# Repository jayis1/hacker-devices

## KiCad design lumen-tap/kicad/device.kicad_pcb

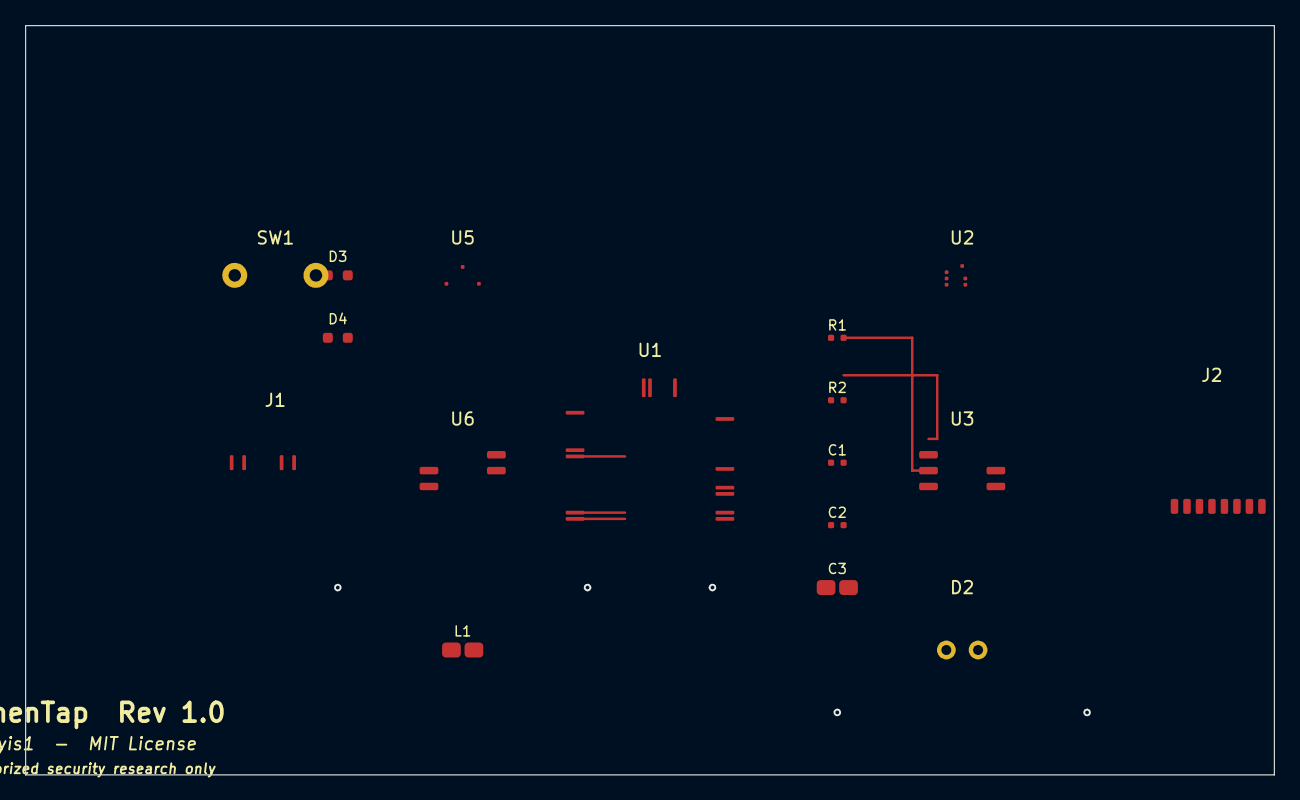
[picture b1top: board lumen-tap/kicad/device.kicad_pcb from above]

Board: 4 copper layers, 100.0 x 60.0 mm, 17 parts (0 on the bottom side), 14 nets.

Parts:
C1, C2: 100nF; C_0402_1005Metric
C3: 10uF; C_0805_2012Metric
D2: S1223; TO-5-2_Window
D3: LED_GREEN; LED_0603_1608Metric
D4: LED_RED; LED_0603_1608Metric
J1: USB_C; USB_C_Receptacle_HRO_TYPE-C-31-M-12
J2: Micro_SD_Card; microSD_HC_Hirose_DM3D-SF
L1: 4u7H; L_0805_2012Metric
R1: 10k; R_0402_1005Metric
R2: 100; R_0402_1005Metric
SW1: SW_SPST_KEYED; SW_PUSH_6mm
U1: STM32H743VIT6; LQFP-100_14x14mm_P0.5mm
U2: iC-HK; QFN-16-1EP_3x3mm_P0.5mm
U3: OPA380; SOIC-8_3.9x4.9mm_P1.27mm
U5: LT3045IDE; DFN-12-1EP_3x3mm_P0.45mm
U6: MP1584EN; SOIC-8_3.9x4.9mm_P1.27mm

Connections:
ARM_KEY: SW1.1, U1.39
GND: C1.2, C2.2, C3.2, D3.2, D4.2, J1.A1, J2.6, R2.2, U1.10, U2.16, U3.4, U5.11, U6.1
LASER_A: R2.1, U2.5
LASER_EN: U1.40, U2.3
LASER_PWM: U1.26, U2.2
LED_FAULT: D4.1, U1.36
LED_STATUS: D3.1, U1.35
PD_ANODE: D2.2, R1.1, U3.3
SD_CLK: J2.5, U1.51
TIA_OUT: R1.2, U3.2, U3.6
VBUS: J1.A4, U1.27
VCC_3V3: C1.1, J2.4, L1.2, SW1.2, U1.11, U6.6, U6.7
VCC_5V: C3.1, L1.1, U5.1, U6.2
VCC_5V_CLEAN: C2.1, U2.1, U3.7, U5.2

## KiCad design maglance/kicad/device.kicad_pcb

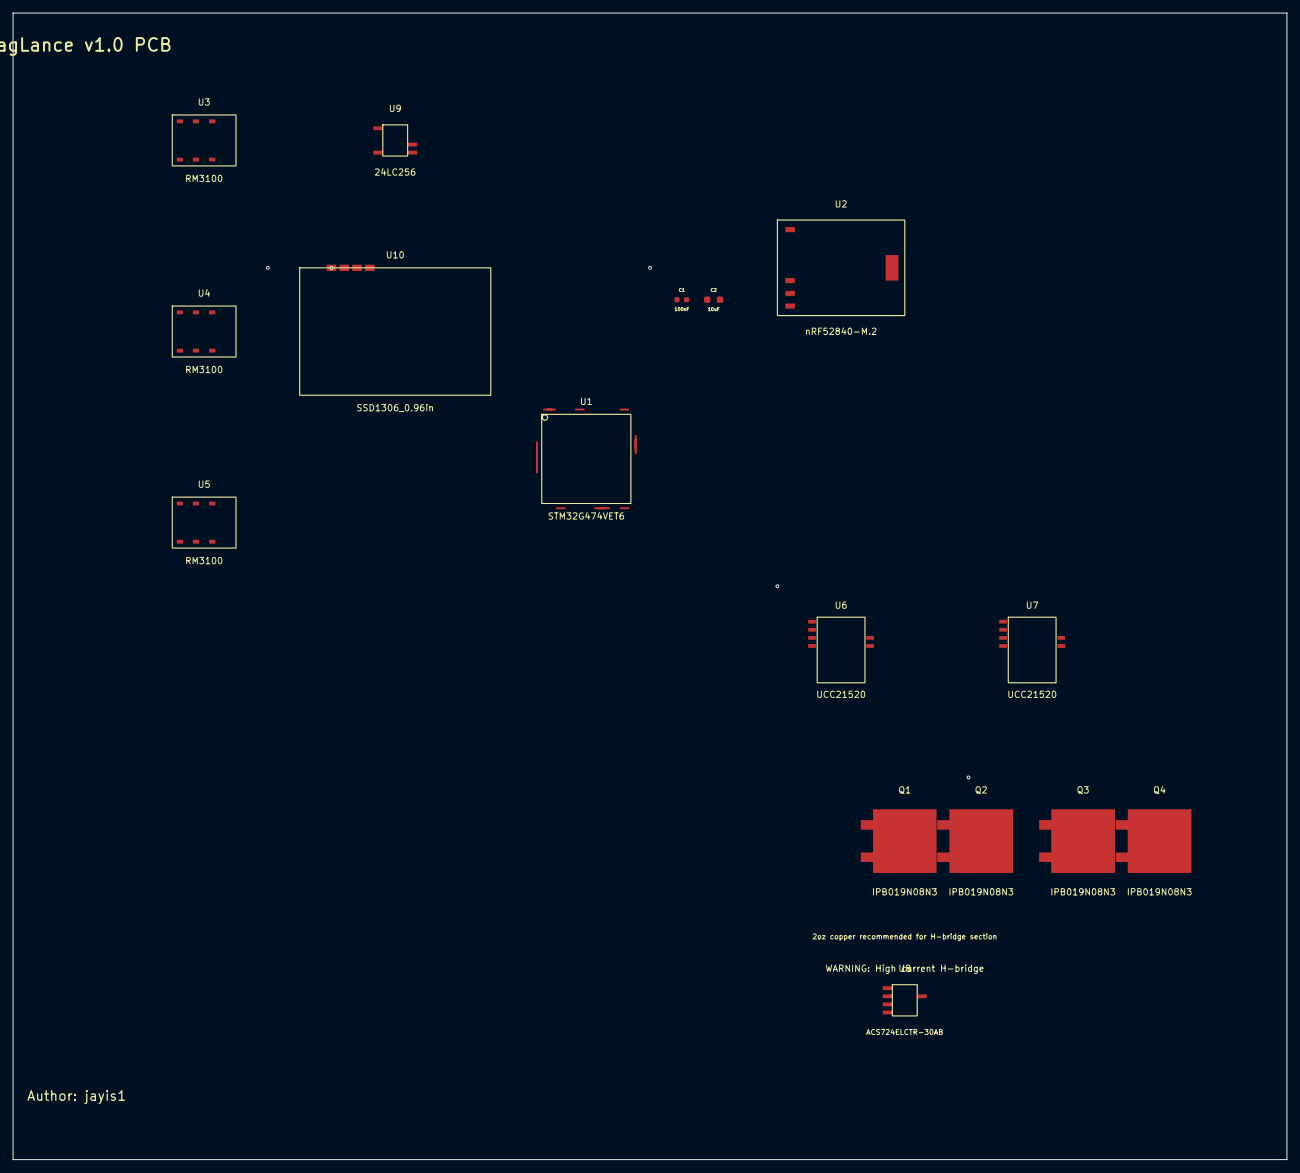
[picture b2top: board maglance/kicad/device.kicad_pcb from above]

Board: 4 copper layers, 200.0 x 180.0 mm, 16 parts (0 on the bottom side), 21 nets, no tracks yet.

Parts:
C1: 100nF; C_0603_1608Metric
C2: 10uF; C_0805_2012Metric
Q1, Q2, Q3, Q4: IPB019N08N3; TO-263-3_TabPin2
U1: STM32G474VET6; LQFP-100_14x14mm_P0.5mm
U2: nRF52840-M.2; Nordic_nRF52840_M2
U3, U4, U5: RM3100; PNI_RM3100
U6, U7: UCC21520; SOIC-16W_7.5x10.3mm_P1.27mm
U8: ACS724ELCTR-30AB; SOIC-8_3.9x4.9mm_P1.27mm
U9: 24LC256; SOIC-8_3.9x4.9mm_P1.27mm
U10: SSD1306_0.96in; OLED_0.96in_128x64

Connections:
+5V: C1.1, C2.1, Q1.2, Q4.2, U1.11, U2.1, U3.1, U4.1, U5.1, U6.1, U7.1, U8.1, U9.8, U10.1
ADC_CURRENT: U1.14, U8.3
COIL+: Q1.3, Q2.2, U8.4
COIL-: Q3.2, Q4.3, U8.5
GATE_Q1: Q1.1, U6.5
GATE_Q2: Q2.1, U6.6
GATE_Q3: Q3.1, U7.5
GATE_Q4: Q4.1, U7.6
GND: C1.2, C2.2, Q2.3, Q3.3, U1.2, U1.27, U2.2, U3.2, U4.2, U5.2, U6.2, U7.2, U8.2, U9.4, U10.2
HRTIM_CHA1: U1.41, U6.3
HRTIM_CHA2: U1.42, U6.4
HRTIM_CHC1: U1.43, U7.3
HRTIM_CHC2: U1.44, U7.4
I2C1_SCL: U1.59, U9.6, U10.3
I2C1_SDA: U1.60, U9.5, U10.4
MAG_CS0: U1.56, U3.6
MAG_CS1: U1.57, U4.6
MAG_CS2: U1.58, U5.6
SPI2_MISO: U1.54, U3.4, U4.4, U5.4
SPI2_MOSI: U1.55, U3.5, U4.5, U5.5
SPI2_SCK: U1.53, U3.3, U4.3, U5.3

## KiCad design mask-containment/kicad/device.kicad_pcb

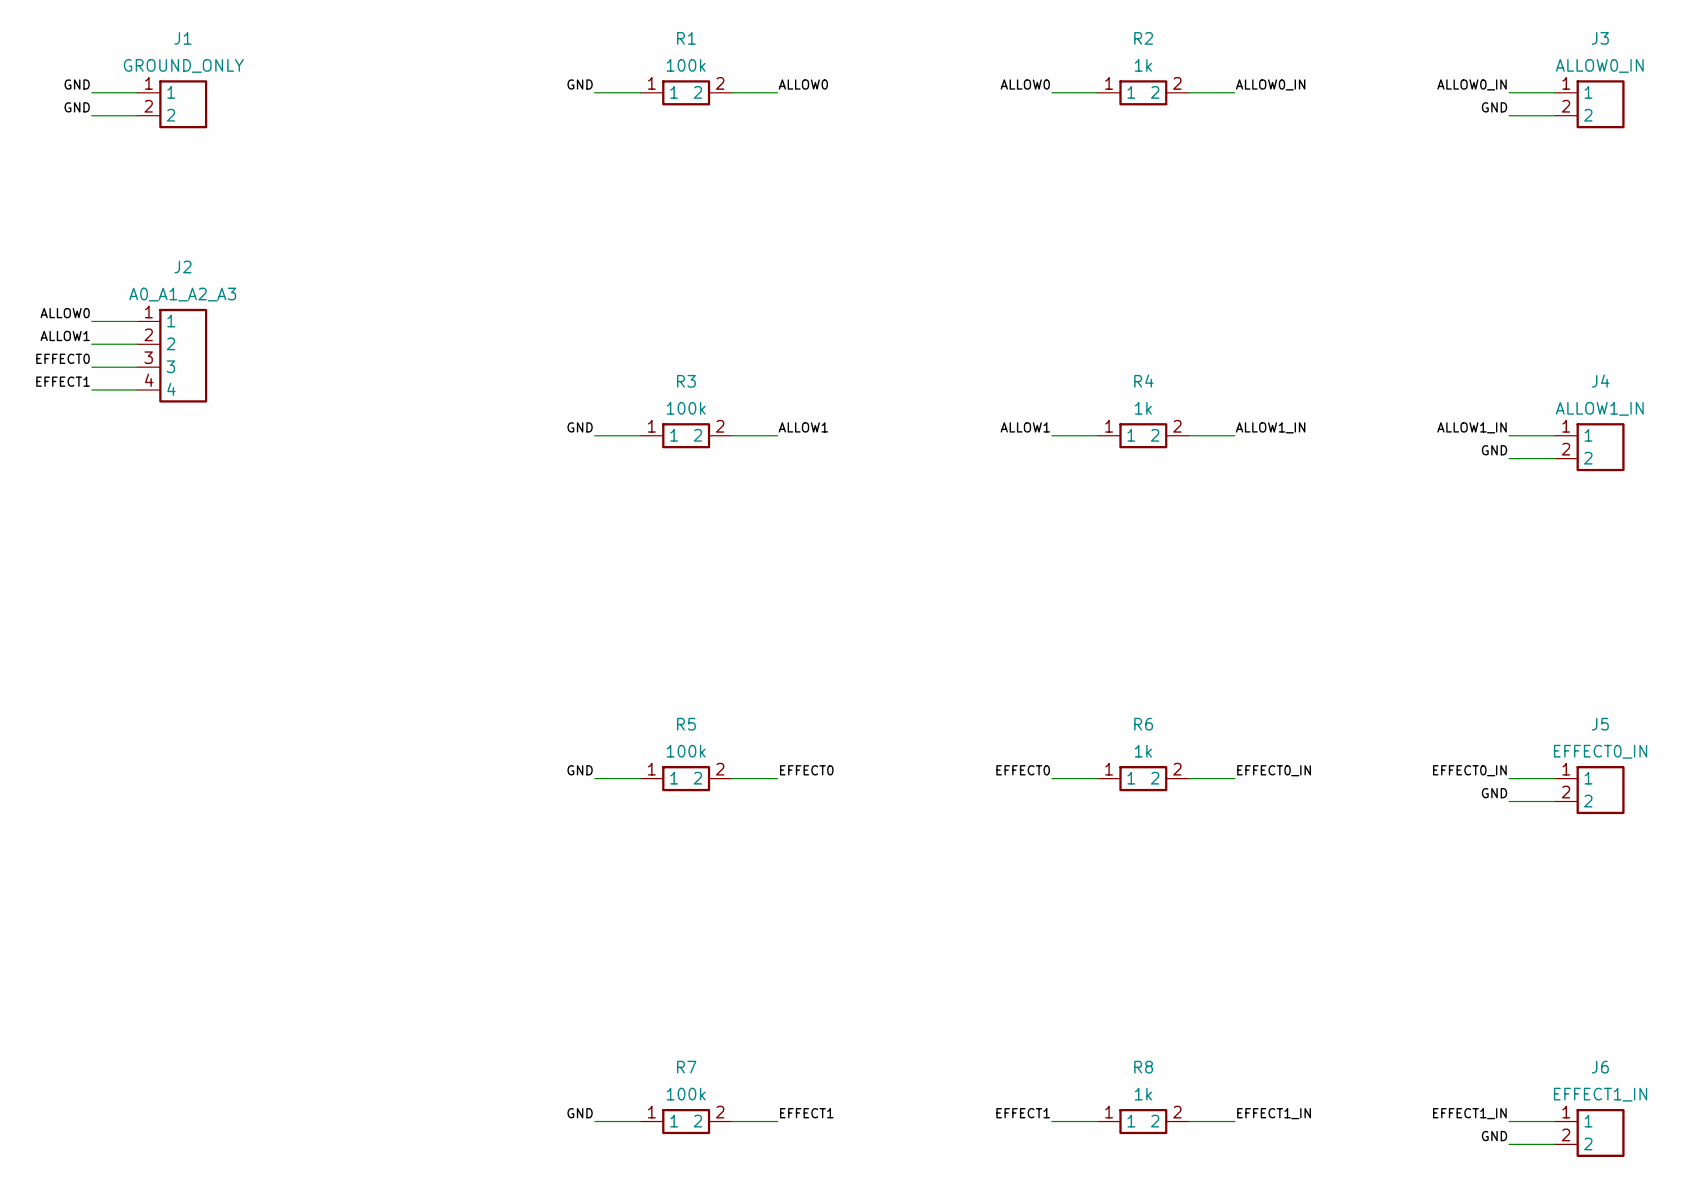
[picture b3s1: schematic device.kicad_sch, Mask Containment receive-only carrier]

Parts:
J1: GROUND_ONLY; PinHeader_1x02_P2.54mm_Vertical
J2: A0_A1_A2_A3; PinHeader_1x04_P2.54mm_Vertical
J3: ALLOW0_IN; PinHeader_1x02_P2.54mm_Vertical
J4: ALLOW1_IN; PinHeader_1x02_P2.54mm_Vertical
J5: EFFECT0_IN; PinHeader_1x02_P2.54mm_Vertical
J6: EFFECT1_IN; PinHeader_1x02_P2.54mm_Vertical
R1, R3, R5, R7: 100k; R_Axial_DIN0207_L6.3mm_D2.5mm_P7.62mm_Horizontal
R2, R4, R6, R8: 1k; R_Axial_DIN0207_L6.3mm_D2.5mm_P7.62mm_Horizontal

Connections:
ALLOW0: J2.1, R1.2, R2.1
ALLOW0_IN: J3.1, R2.2
ALLOW1: J2.2, R3.2, R4.1
ALLOW1_IN: J4.1, R4.2
EFFECT0: J2.3, R5.2, R6.1
EFFECT0_IN: J5.1, R6.2
EFFECT1: J2.4, R7.2, R8.1
EFFECT1_IN: J6.1, R8.2
GND: J1.1, J1.2, J3.2, J4.2, J5.2, J6.2, R1.1, R3.1, R5.1, R7.1

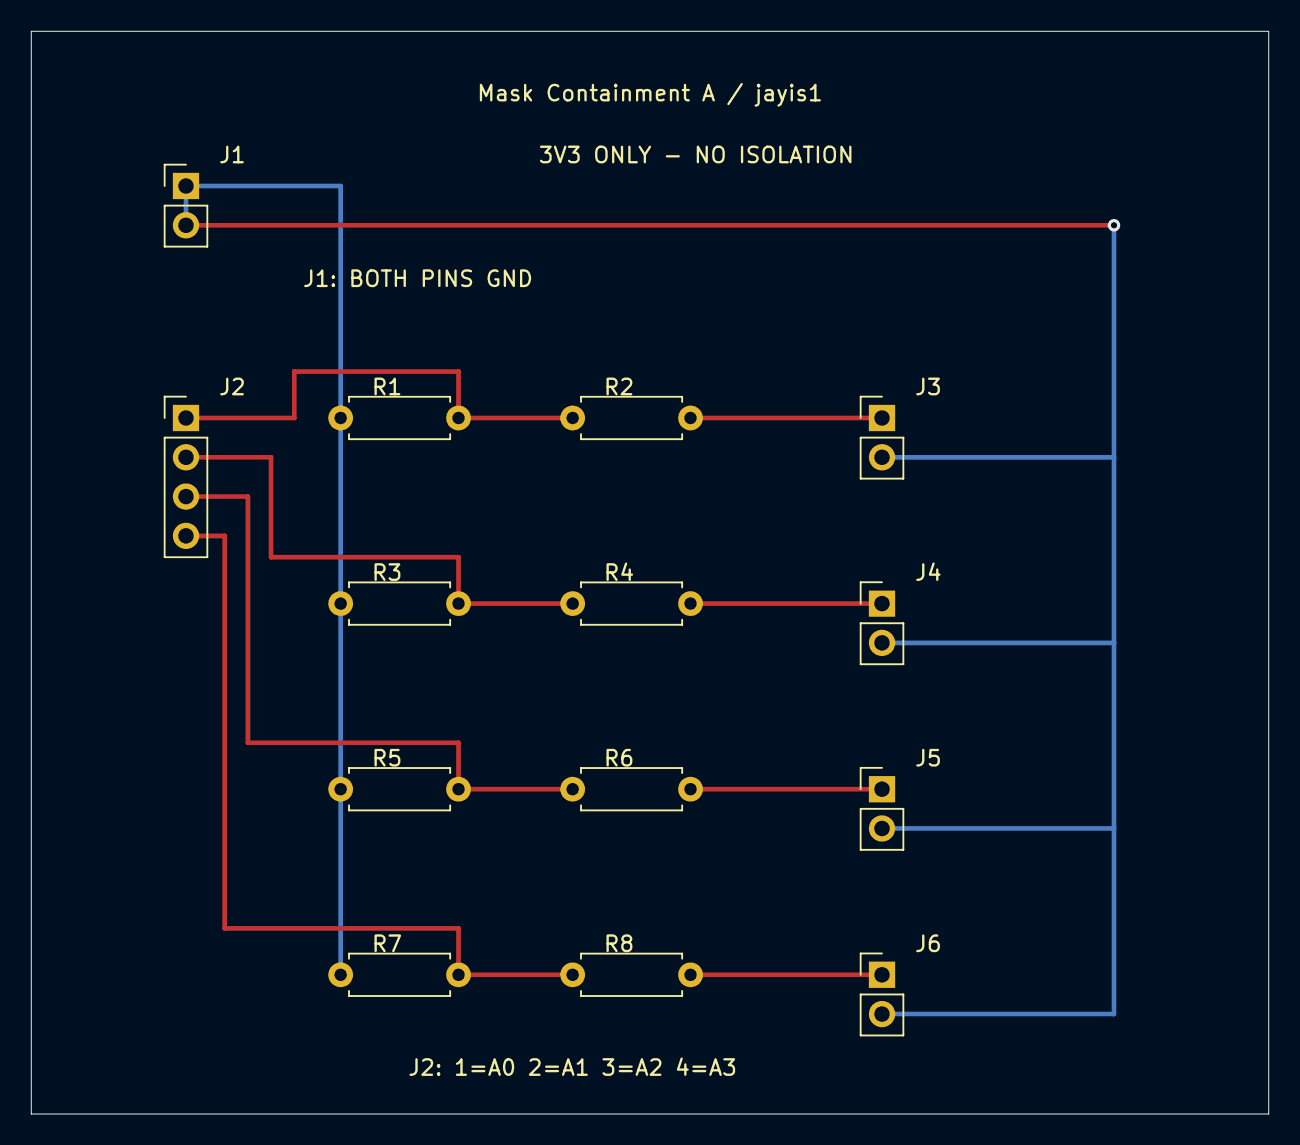
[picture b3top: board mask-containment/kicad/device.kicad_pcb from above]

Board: 2 copper layers, 80.0 x 70.0 mm, 14 parts (0 on the bottom side), 9 nets.

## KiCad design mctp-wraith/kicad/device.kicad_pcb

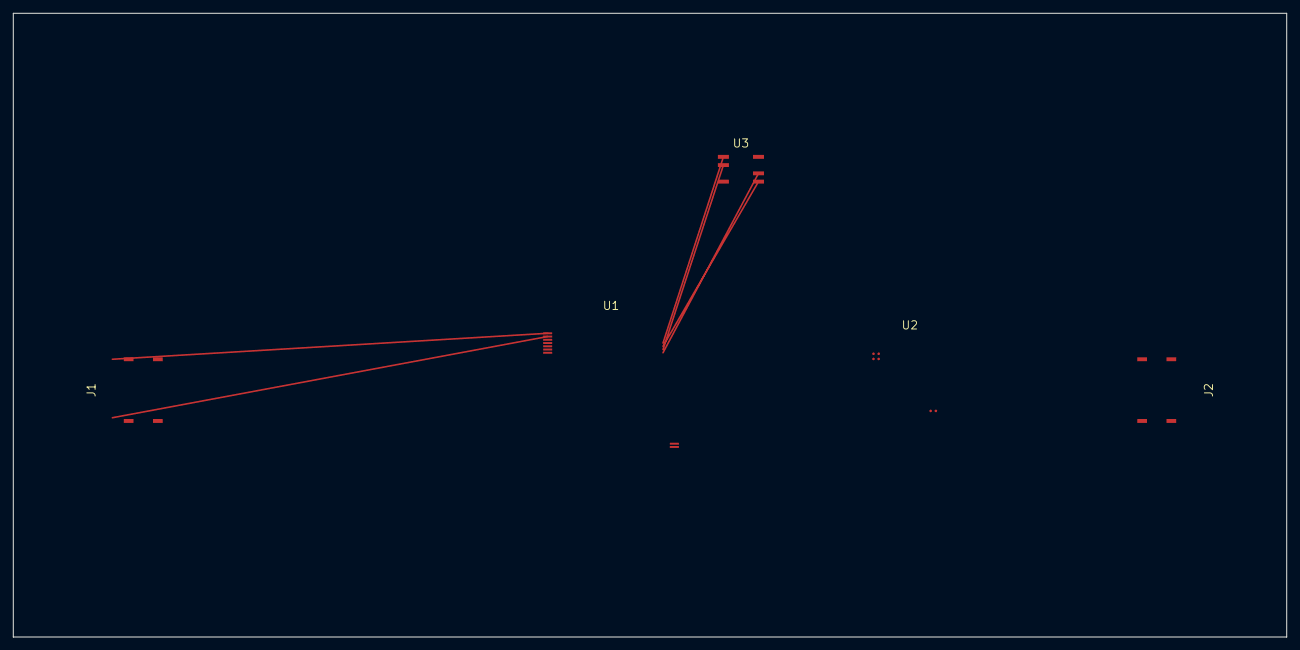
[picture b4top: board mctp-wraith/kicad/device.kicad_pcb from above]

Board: 2 copper layers, 196.0 x 96.0 mm, 5 parts (0 on the bottom side), 11 nets.

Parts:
J1: UPSTREAM_SIDEBAND; Samtec_QSH-020-01-L-D-A
J2: DOWNSTREAM_SIDEBAND; Samtec_QSH-020-01-L-D-A
U1: STM32H753ZITx; LQFP-144_20x20mm_P0.5mm
U2: LFE5U-25F; caBGA-256_14x14_0.8mm
U3: W25Q128JVSIQ; SOIC-8_5.23x5.23mm_P1.27mm

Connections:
ALERT_N: J1.19, J2.19, U1.7
GND: J1.20, J2.20, U1.73, U2.N12, U3.4
I3C_SCL_DN: J2.1, U2.A1
I3C_SCL_UP: J1.1, U1.1, U2.B1
I3C_SDA_DN: J2.2, U2.A2
I3C_SDA_UP: J1.2, U1.2, U2.B2
QSPI_CLK: U1.4, U3.6
QSPI_CS: U1.3, U3.1
QSPI_IO0: U1.5, U3.2
QSPI_IO1: U1.6, U3.5
VCC_3V3: U1.72, U2.M12, U3.8

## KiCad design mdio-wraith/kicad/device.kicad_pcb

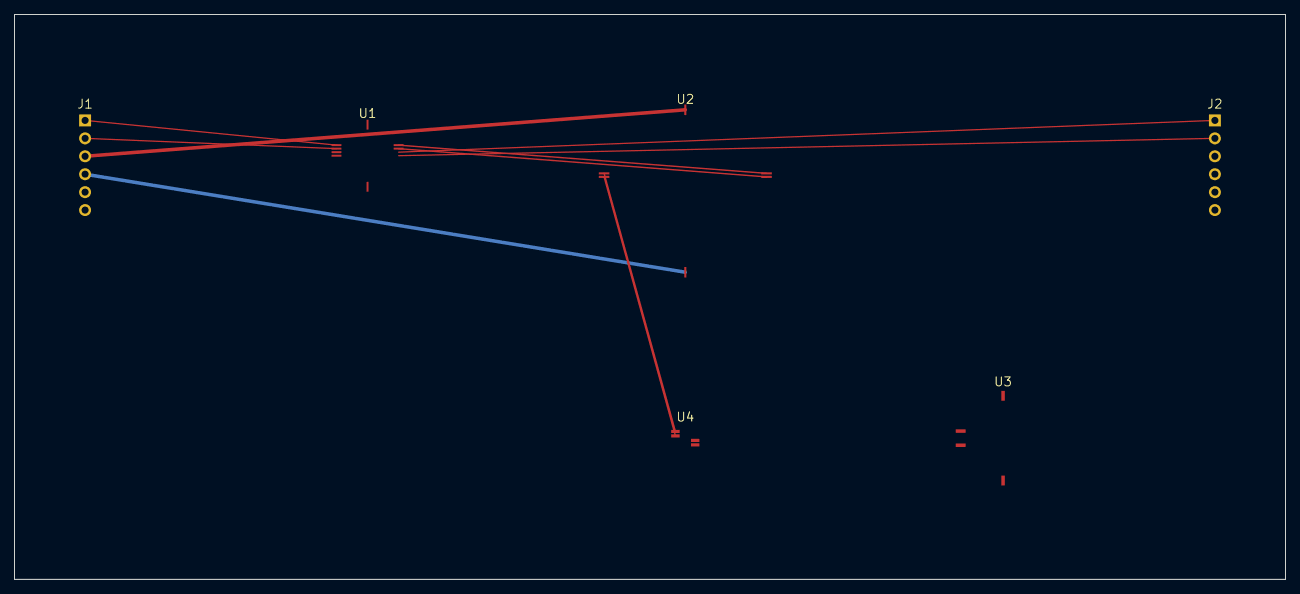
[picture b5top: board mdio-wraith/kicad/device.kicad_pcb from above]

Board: 2 copper layers, 180.0 x 80.0 mm, 6 parts (0 on the bottom side), 10 nets.

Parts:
J1: HOST_MDIO_CLIP; PinHeader_1x06_P2.54mm_Vertical
J2: PHY_MDIO_CLIP; PinHeader_1x06_P2.54mm_Vertical
U1: CrossLink-NX; LQFP-48_7x7mm_P0.5mm
U2: STM32H723ZGT6; LQFP-144_20x20mm_P0.5mm
U3: ESP32-C6-MINI-1
U4: INA232AIDDFR; SOT-23-8

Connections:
3V3: J1.3, J2.3, U1.62, U2.13, U3.1, U4.6
GND: J1.4, J2.4, U1.31, U2.64, U3.15, U4.5
I2C_SCL: J2.5, U2.95, U4.1
I2C_SDA: J2.6, U2.96, U4.2
MDC_HOST: J1.2, U1.6
MDC_PHY: J2.2, U1.8
MDIO_HOST: J1.1, U1.5
MDIO_PHY: J2.1, U1.7
UART_RX: J1.6, U1.45, U2.52, U3.31
UART_TX: J1.5, U1.44, U2.51, U3.30

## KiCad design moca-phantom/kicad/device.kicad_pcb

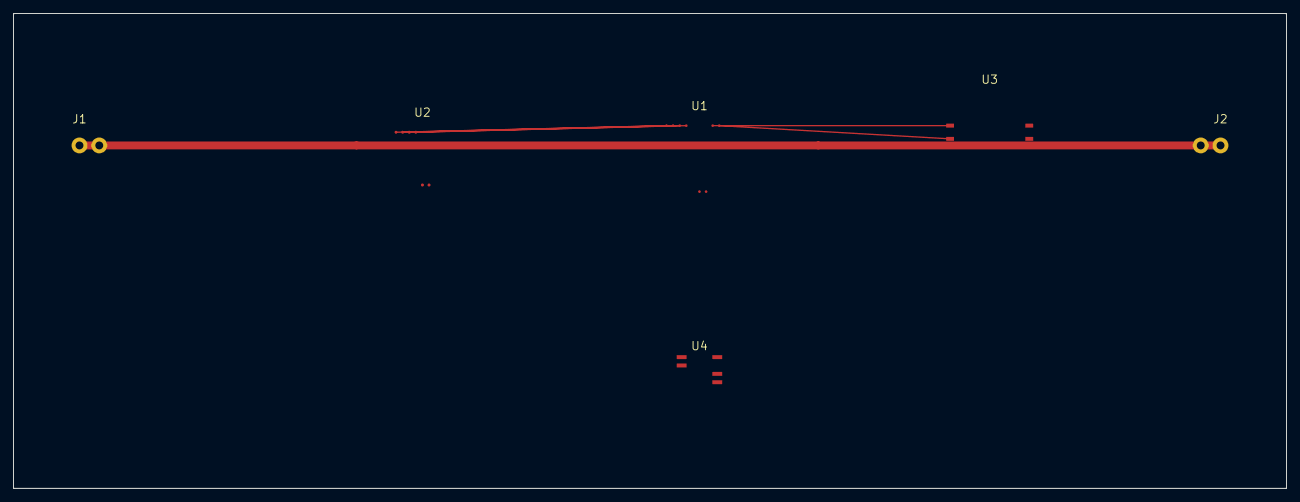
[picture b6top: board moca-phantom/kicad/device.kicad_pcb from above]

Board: 2 copper layers, 193.0 x 72.0 mm, 6 parts (0 on the bottom side), 9 nets.

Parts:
J1: F_IN; Conn_F
J2: F_OUT; Conn_F
U1: i.MXRT1176; BGA-529_19x19_12.0x12.0mm
U2: CrossLink-NX; BGA-289_14x14_10.0x10.0mm
U3: ESP32-C6-WROOM-1
U4: W25Q256JV; SOIC-8_3.9x4.9mm_P1.27mm

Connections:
3V3: U1.P1, U2.P1, U3.3, U4.8
COAX_PATH: J1.1, J2.1
FPGA_INT: U1.A4, U2.A4
GND: J1.2, J2.2, U1.P2, U2.P2, U3.4, U4.4
MCU_SPI_MISO: U1.A2, U2.A2, U4.2
MCU_SPI_MOSI: U1.A1, U2.A1, U4.1
MCU_SPI_SCK: U1.A3, U2.A3, U4.6
MCU_UART_RX: U1.B2, U3.2
MCU_UART_TX: U1.B1, U3.1

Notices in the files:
lumen-tap/kicad/device.kicad_pcb:
Author: jayis1 - MIT License
lumen-tap/kicad/device.kicad_sch:
MIT License - authorized security research only
Author: jayis1  |  MIT License  |  Authorized security research only
maglance/kicad/device.kicad_pcb:
License: GPL-2.0 / CERN-OHL-S v2
